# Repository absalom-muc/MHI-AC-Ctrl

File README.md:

# MHI-AC-Ctrl
Reads and writes data (e.g. power, mode, fan status etc.) from/to a Mitsubishi Heavy Industries (MHI) air conditioner (AC) via SPI controlled by MQTT. The AC is the SPI master and the ESP8266 is the SPI slave.

# Attention:
:warning: You have to open the indoor unit to have access to the SPI. Opening of the indoor unit should be done by 
a qualified professional because faulty handling may cause leakage of water, electric shock or fire! :warning: 

# Prerequisites:
For use of the program you have to connect your ESP8266 (I use a LOLIN(WEMOS) D1 R2 & mini with 80 MHz) via a
cable connector to your air conditioner. This has to be a split device (separated indoor and outdoor unit).
I assume that all AC units of the type "SRK xx ZS-S" / "SRC xx ZS-S" are supported. I use the indoor unit SRK 35 ZS-S and the outdoor unit SRC 35 ZS-S. Users reported that additionally the following models are supported:

- [SRF xx ZJX-S1](https://github.com/absalom-muc/MHI-AC-Ctrl/issues/17#issue-632187165)
- [SRF xx ZMX-S](https://github.com/absalom-muc/MHI-AC-Ctrl/issues/17#issuecomment-704789297)
- [SRF xx ZMXA-S](https://github.com/absalom-muc/MHI-AC-Ctrl/pull/91)
- SRF xx ZF-W
- [SRF xx ZS-W](https://github.com/absalom-muc/MHI-AC-Ctrl/pull/216#issue-3234769567) works with frame size 20
- [SRK xx ZJ-S](https://github.com/absalom-muc/MHI-AC-Ctrl/issues/10)
- [SRK xx ZM-S](https://github.com/absalom-muc/MHI-AC-Ctrl/issues/9)
- [SRK xx ZJX-S](https://github.com/absalom-muc/MHI-AC-Ctrl/issues/17#issuecomment-646469621)
- [SRK xx ZJX-S1](https://github.com/absalom-muc/MHI-AC-Ctrl/issues/17#issuecomment-646968940)
- [SRK xx ZR-WF](https://github.com/absalom-muc/MHI-AC-Ctrl/issues/214)
- [SRK xx ZRA-W](https://github.com/absalom-muc/MHI-AC-Ctrl/issues/17#issuecomment-730628655) / DXK xx ZRA-W
- [SRK xx ZSA-W](https://github.com/absalom-muc/MHI-AC-Ctrl/issues/17#issuecomment-891649495) / DXK xx ZSA-W
- [SRK63ZSPR-S](https://github.com/absalom-muc/MHI-AC-Ctrl/issues/149)
- SRK xx ZSXA-W/A
- [SRK xx ZSX-S](https://github.com/absalom-muc/MHI-AC-Ctrl/issues/6#issuecomment-582242372)
- [SRK xx ZSX-W](https://github.com/absalom-muc/MHI-AC-Ctrl/issues/17#issuecomment-643748095)
- [SRK xx ZS-W](https://github.com/absalom-muc/MHI-AC-Ctrl/issues/121)
- [SRK xx ZS-WF](https://github.com/absalom-muc/MHI-AC-Ctrl/issues/121#issuecomment-1938350129)
- [SRC 35Z SA-W]
- [DXK xx ZMA-S](https://github.com/absalom-muc/MHI-AC-Ctrl/issues/201)
- [SRK 2824 T (Japanese domestic model)](https://github.com/absalom-muc/MHI-AC-Ctrl/issues/211)

Unsupported models:
- [SRK71ZEA-S1](https://github.com/absalom-muc/MHI-AC-Ctrl/issues/143)
- [SRK35ZC-S](https://github.com/absalom-muc/MHI-AC-Ctrl/issues/154)
- [SRK xx ZSPR-S](https://github.com/absalom-muc/MHI-AC-Ctrl/issues/200) (except SRK63ZSPR-S)

If you find out that also other models are supported that are not listed here, please give feedback so that I can expand the list. In general, please recheck if your AC has a CNS connector before you spend time and money to build the hardware.

# Installing:

## Hardware:
The ESP8266 is powered from the AC via DC-DC (12V -> 5V) converter. 
The ESP8266 SPI signals SCL (SPI clock), MOSI (Master Out Slave In) and MISO (Master In Slave Out) are connected via a voltage level shifter 5V <-> 3.3V with the AC. Direct connection of the signals without a level shifter could damage your ESP8266!
More details are described in [Hardware.md](Hardware.md).

## Software:
The program uses the following libraries:
 - MQTT client library [PubSubClient3](https://github.com/hmueller01/pubsubclient3)
   - :warning: Don't use PubSubClient v2.8.0, it is broken due to issue [#747](https://github.com/knolleary/pubsubclient/issues/747) :warning:
 - [ArduinoOTA](https://github.com/esp8266/Arduino/tree/master/libraries/ArduinoOTA) (might be removed in future)
 
and optionally you need for the use of an external temperature sensor DS18x20 the libraries
 - [OneWire](https://www.pjrc.com/teensy/td_libs_OneWire.html)
 - [DallasTemperature](https://github.com/milesburton/Arduino-Temperature-Control-Library)

Please check the GitHub pages to see how to install them (usually via tools -> libraries).

Create a sub-directory "MHI-AC-Ctrl" and copy the files from the latest [release](https://github.com/absalom-muc/MHI-AC-Ctrl/releases) src directory in your MHI-AC-Ctrl sub-directory. You could also use the recently updated version in the [src folder](src) but with the risk that it is more unstable. The stability of the program is better when you compile it for a CPU frequency of 160MHz.
The configuration options are described in [SW-Configuration.md](SW-Configuration.md).

In a previous version (see [here](https://github.com/absalom-muc/MHI-AC-SPY)) I used the Hardware-SPI of the ESP8266. But since the SPI documentation of ESP8266 is poor, I decided to switch to a Software based SPI.
This Software based SPI is reliable and the performance of the ESP8266 is sufficient for this use case.
In case of problems please check the [Troubleshooting guide](Troubleshooting.md).

# Enhancement
If you are interested to have a deeper look on the SPI protocol or want to trace the SPI signals, please check [MHI-AC-Trace](https://github.com/absalom-muc/MHI-AC-Trace). But this is not needed for the standard user of MHI-AC-Ctrl.

# License
This project is licensed under the MIT License - see the LICENSE.md file for details

# Acknowledgments
The coding of the [SPI protocol](https://github.com/absalom-muc/MHI-AC-Trace/blob/main/SPI.md) of the AC is a nightmare. Without [rjdekker's MHI2MQTT](https://github.com/rjdekker/MHI2MQTT) I had no chance to understand the protocol! Unfortunately rjdekker is no longer active on GitHub. He used an Arduino plus an ESP8266 for his project.
Also thank you very much on the authors and contributors of [MQTT client](https://github.com/knolleary/pubsubclient), [ArduinoOTA](https://github.com/esp8266/Arduino/tree/master/libraries/ArduinoOTA), [OneWire](https://www.pjrc.com/teensy/td_libs_OneWire.html) and [DallasTemperature](https://github.com/milesburton/Arduino-Temperature-Control-Library) libraries.

Last but not least thank you for the implementation of MHI-AC-Ctrl in [different environments](https://github.com/absalom-muc/MHI-AC-Ctrl/blob/master/SW-Configuration.md#integration-examples) (FHEM, Tasmota, Home Assistant etc.)

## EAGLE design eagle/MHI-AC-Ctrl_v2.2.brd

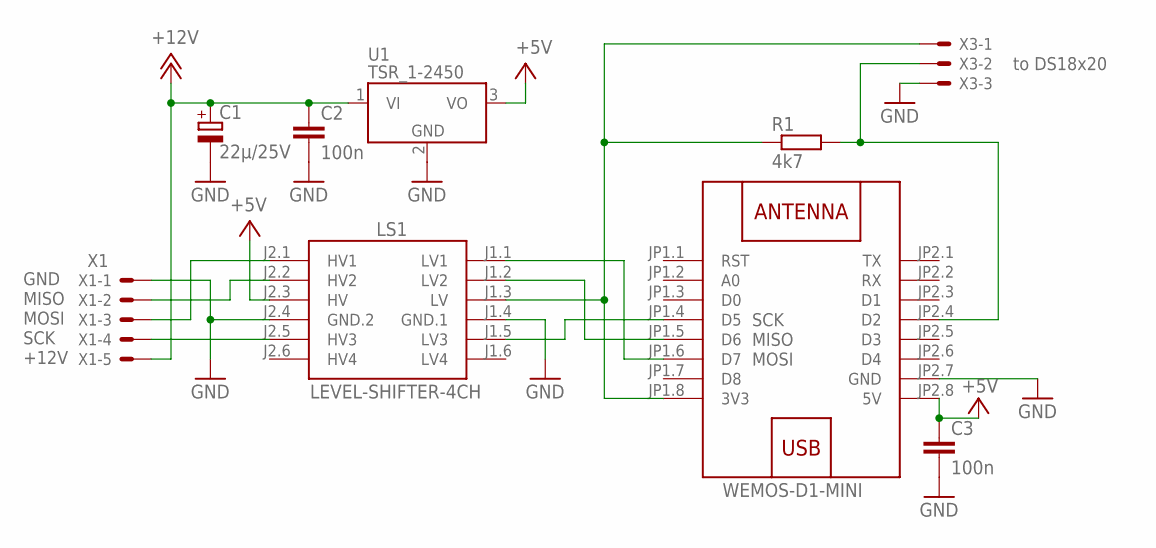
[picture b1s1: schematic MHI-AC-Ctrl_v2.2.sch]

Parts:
C1: 22µ/25V; E15-5
C2, C3: 100n; C025-024X044
LS1: LEVEL-SHIFTER-4CH
R1: 4k7; 0207/10
U1: TSR_1-2450; TSR-1
U$1: WEMOS-D1-MINI
X1: JST 03JQ-BT; JST-XH-05-PACKAGE-LONG-PAD
X3: JST-XH-03-PIN; JST-XH-03-ST90-PACKAGE-LONG-PAD

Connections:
+3V3: LS1.J1.3 (LV), R1.1, U$1.JP1.8 (3V3), X3.1
+5V: C3.1, LS1.J2.3 (HV), U1.3 (VO), U$1.JP2.8 (5V)
+12V: C1.+, C2.1, U1.1 (VI), X1.5
D2: R1.2, U$1.JP2.4 (D2), X3.2
GND: C1.-, C2.2, C3.2, LS1.J1.4 (GND.1), LS1.J2.4 (GND.2), U1.2 (GND), U$1.JP2.7 (GND), X1.1, X3.3
MISO: LS1.J2.2 (HV2), X1.2
MISO_LV: LS1.J1.2 (LV2), U$1.JP1.5 (D6)
MOSI: LS1.J2.1 (HV1), X1.3
MOSI_LV: LS1.J1.1 (LV1), U$1.JP1.6 (D7)
SCK: LS1.J2.5 (HV3), X1.4
SCK_LV: LS1.J1.5 (LV3), U$1.JP1.4 (D5)

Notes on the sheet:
MOSI
MISO
SCK
to DS18x20

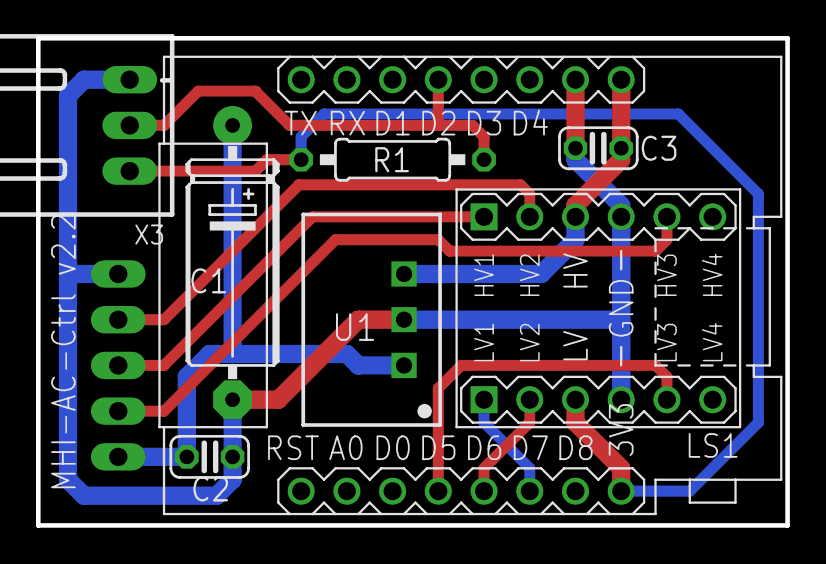
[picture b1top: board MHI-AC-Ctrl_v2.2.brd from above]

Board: 2 copper layers, 41.6 x 27.1 mm, 9 parts (1 on the bottom side), 11 nets.

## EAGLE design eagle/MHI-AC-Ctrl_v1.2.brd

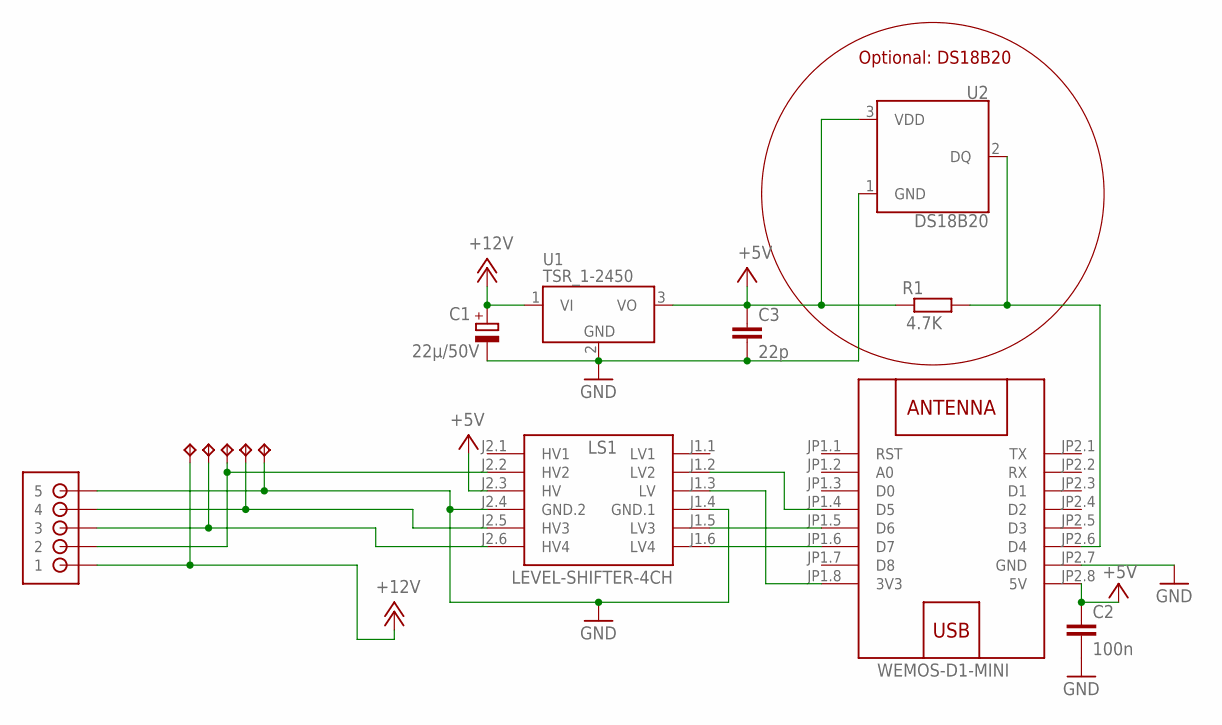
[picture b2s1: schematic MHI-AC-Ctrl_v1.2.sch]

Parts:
C1: 22µ/50V; E5-10,5
C2: 100n; C025-024X044
C3: 22p; C025-024X044
LS1: LEVEL-SHIFTER-4CH
R1: 4.7K; 0204/7
TP9, TP10, TP11, TP12, TP13: TPPAD1-13; P1-13
U1: TSR_1-2450; TSR-1
U2: DS18B20; TO-92-TO92127P495H2044-3
U$1: WEMOS-D1-MINI
U$4: JST-PH_5-PIN_HEADER; JST_B5B-PH_HEADER

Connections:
+3V3: LS1.J1.3 (LV), U$1.JP1.8 (3V3)
+5V: C2.1, C3.1, LS1.J2.3 (HV), R1.2, U1.3 (VO), U2.3 (VDD), U$1.JP2.8 (5V)
+12V: C1.+, TP13.TP, U1.1 (VI), U$4.P1 (1)
GND: C1.-, C2.2, C3.2, LS1.J1.4 (GND.1), LS1.J2.4 (GND.2), TP9.TP, U1.2 (GND), U2.1 (GND), U$1.JP2.7 (GND), U$4.P5 (5)
MISO: LS1.J2.5 (HV3), TP10.TP, U$4.P4 (4)
unnamed: LS1.J1.5 (LV3), U$1.JP1.5 (D6)
unnamed: LS1.J1.6 (LV4), U$1.JP1.6 (D7)
unnamed: LS1.J2.2 (HV2), TP11.TP, U$4.P2 (2)
unnamed: LS1.J2.6 (HV4), TP12.TP, U$4.P3 (3)
unnamed: R1.1, U2.2 (DQ), U$1.JP2.6 (D4)
SCL_LV: LS1.J1.2 (LV2), U$1.JP1.4 (D5)

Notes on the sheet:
Optional: DS18B20

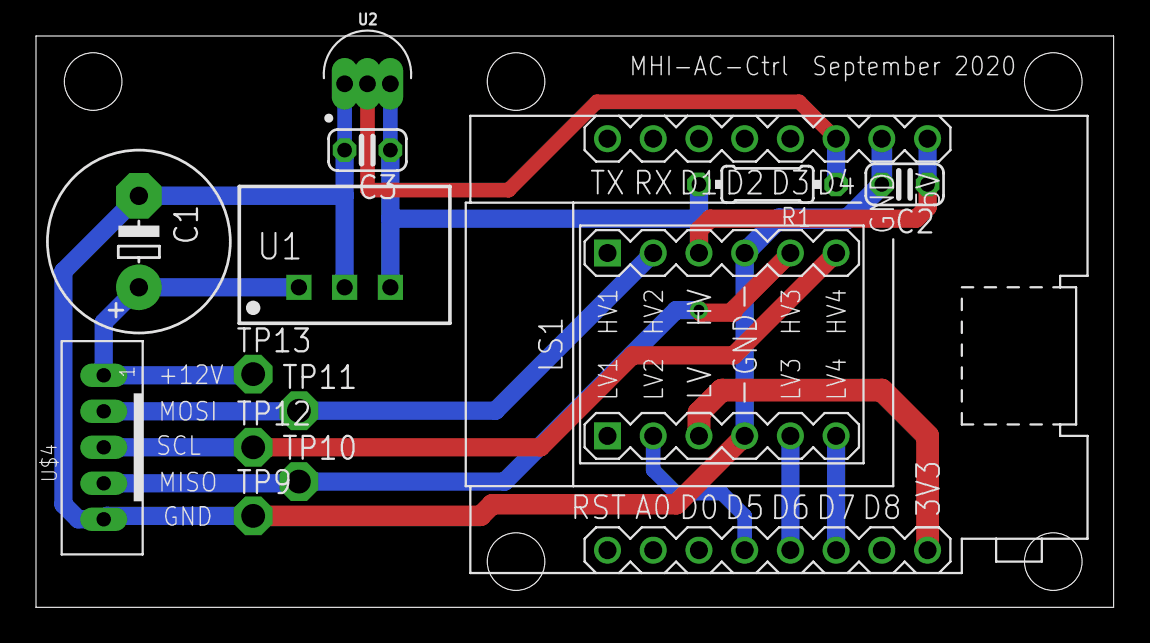
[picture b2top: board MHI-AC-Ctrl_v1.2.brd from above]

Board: 2 copper layers, 59.9 x 31.7 mm, 14 parts (0 on the bottom side), 11 nets.

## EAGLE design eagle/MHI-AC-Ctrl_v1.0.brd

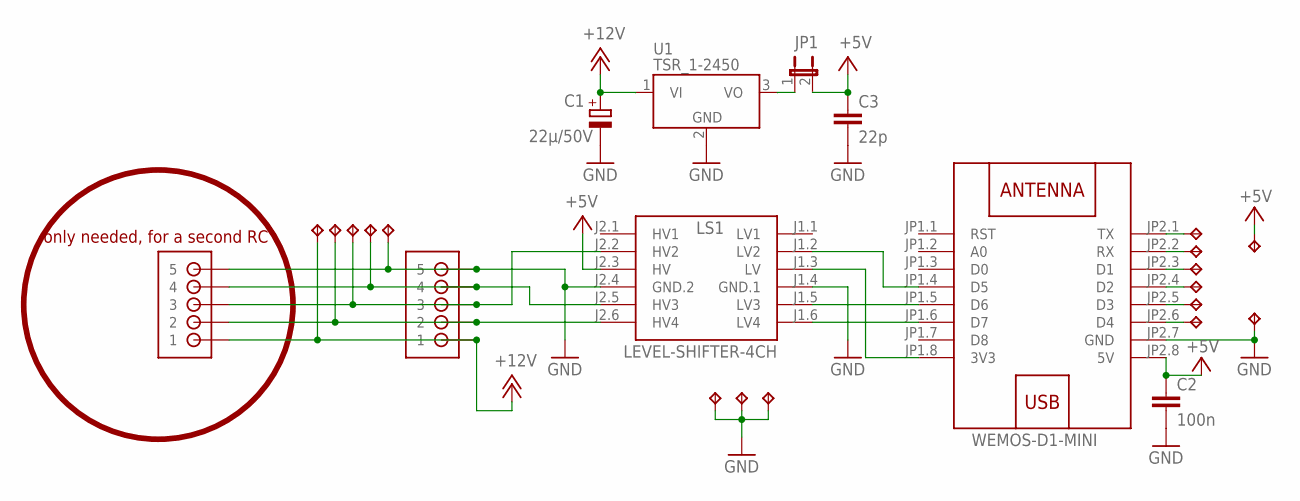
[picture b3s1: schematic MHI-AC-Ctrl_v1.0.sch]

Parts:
C1: 22µ/50V; E5-10,5
C2: 100n; C025-024X044
C3: 22p; C025-024X044
JP1: JP1E; JP1
LS1: LEVEL-SHIFTER-4CH
TP1, TP2, TP3, TP4, TP5, TP6, TP7, TP8, TP9, TP10, TP11, TP12, TP13, TP14, TP15, TP16: TPPAD1-13; P1-13
U1: TSR_1-2450; TSR-1
U$1: WEMOS-D1-MINI
U$4, U$5: JST-PH_5-PIN_HEADER; JST_B5B-PH_HEADER

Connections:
+3V3: LS1.J1.3 (LV), U$1.JP1.8 (3V3)
+5V: C2.1, C3.1, JP1.2, LS1.J2.3 (HV), TP8.TP, U$1.JP2.8 (5V)
+12V: C1.+, TP13.TP, U1.1 (VI), U$4.P1 (1), U$5.P1 (1)
GND: C1.-, C2.2, C3.2, LS1.J1.4 (GND.1), LS1.J2.4 (GND.2), TP7.TP, TP9.TP, TP14.TP, TP15.TP, TP16.TP, U1.2 (GND), U$1.JP2.7 (GND), U$4.P5 (5), U$5.P5 (5)
MISO: LS1.J2.5 (HV3), TP10.TP, U$4.P4 (4), U$5.P4 (4)
MISO_LV: LS1.J1.5 (LV3), U$1.JP1.5 (D6)
MOSI: LS1.J2.6 (HV4), TP12.TP, U$4.P2 (2), U$5.P2 (2)
MOSI_LV: LS1.J1.6 (LV4), U$1.JP1.6 (D7)
unnamed: TP1.TP, U$1.JP2.1 (TX)
unnamed: TP2.TP, U$1.JP2.2 (RX)
unnamed: TP3.TP, U$1.JP2.3 (D1)
unnamed: TP4.TP, U$1.JP2.4 (D2)
unnamed: TP5.TP, U$1.JP2.5 (D3)
unnamed: TP6.TP, U$1.JP2.6 (D4)
unnamed: JP1.1, U1.3 (VO)
SCL: LS1.J2.2 (HV2), TP11.TP, U$4.P3 (3), U$5.P3 (3)
SCL_LV: LS1.J1.2 (LV2), U$1.JP1.4 (D5)

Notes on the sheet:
only needed, for a second RC

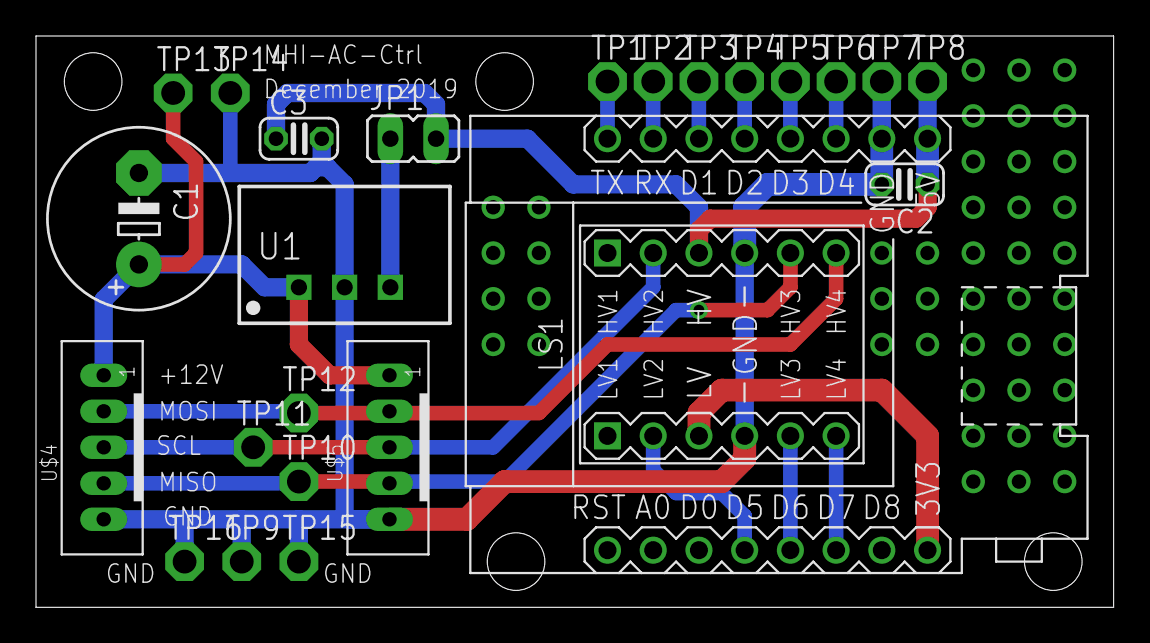
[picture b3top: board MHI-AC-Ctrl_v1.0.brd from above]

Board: 2 copper layers, 59.9 x 31.7 mm, 25 parts (0 on the bottom side), 17 nets.

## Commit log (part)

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2019-12-07 Create tmp
2019-12-15 update for v1.1
    Error code (DB4) added
    OTA is now also working when waiting for a MQTT connection
2019-12-17 Vanes information enhanced
    Due to update from niclet in the thread https://github.com/rjdekker/MHI2MQTT/issues/8#issuecomment-557870093
2019-12-21 some minor corrections
    clarification related to vanes
2019-12-21 configuration images added
2019-12-21 Showing different configurations
2019-12-21 not needed here
2019-12-21 Assembled PCB figure added
2020-01-18 update v1.2
    see Version.md
2020-01-20 Figures labeled
2020-01-20 Connection between AC and remote control clarified
2020-01-27 Fix logic error on MQTT connection failure backoff
2020-03-01 typos for v1.3 corrected
2020-03-01 link for src directory added
2020-03-01 typos corrected
2020-03-01 link to SPI.md added
2020-03-06 Clarification for Vanes status
2020-04-26 Timing diagram frame & byte
2020-04-26 timing diagram and timing values added
2020-04-26 cable connection diagram added
2020-05-14 Added changeable defs for Power and Mode states
2020-05-14 Operation date mode edits
2020-05-14 Updated MQTT readme with overrides
2020-05-14 Added OTA_NAME. Added MQTT_PREFIX example
2020-05-14 Corrected power and mode syntax
2020-06-05 update to v2.0
    see Version.md
2020-06-05 format issue resolved
2020-06-06 bug in row 192 fixed (wrong interrupt handler was selected)
    and some minor code rebuild
2020-06-07 unused variables removed
2020-06-07 write to AC simplified
2020-06-07 comment added
2020-06-12 added supported AC models
2020-06-14 1.Fix the pins are not match definition 2.Support for ESP-01
2020-06-14 Fix power on randomly
2020-06-15 Remove support for ESP-01
2020-06-15 Revert because it's still broken
2020-06-15 fix of issue #18 (AC Power off randomly)
    fix of issue #18 https://github.com/absalom-muc/MHI-AC-Ctrl/issues/18#issuecomment-643739863. The illegal (dummy) value 0xff from opdata was used for MISO_DB6. This led to the shutdown of the air con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
2020-06-15 List of supported AC models enhanced, SW installation description adapted
2020-06-18 link to error code document updated
2020-06-20 supported models added
2020-06-21 Create frequency_measurement.ino
    Used for measurement of the SCK period and byte/frame period
2020-06-24 SPI logger
    logs the timing of the SPI signal edges
2020-06-24 v2.01
    - No functional changes
    - Further reduction of memory usage
    - Compiler warnings removed
    - set-mechanism reworked
    - SCK by SCK_PIN replaced according to [pull request 19](https://github.com/absalom-muc/MHI-AC-Ctrl/pull/19)
    - Shift void MeasureFrequency() from support.cpp to MHI-AC-Ctrl-core.cpp
2020-06-24 v2.01
2020-06-28 update to v2.02
    Functionality for POWERON_WHEN_CHANGING_MODE enhanced, the according #define shifted to support.h
2020-06-28 typo in HOSTNAME corrected
2020-07-01 Made warning clearer not to use PubSubClient v2.8.0
2020-07-01 switched to vcd format
    use e.g. PulseView to see the waveform
2020-07-08 reference to Troubleshooting.md added
2020-07-09 updates for 2.03
    - Functionality for POWERON_WHEN_CHANGING_MODE improved in MHI-AC-Ctrl.ino
    - WiFi mode restricted to STA (no more AP) in support.cpp
2020-07-09 info for fan auto added
2020-07-09 update to v2.1
    generation of vcd improved
2020-07-27 Another supported model
    Hi absalom, thank you very much for this project.
    I successfully installed your adapter yesterday.
    My MHI model is: **SRK 35 ZS-W**
2020-07-27 Fixing link to SERVICE SUPPORT HANDBOOK
2020-07-27 Another supported model (#35)
    Hi absalom, thank you very much for this project.
    I successfully installed your adapter yesterday.
    My MHI model is: **SRK 35 ZS-W**
2020-07-29 link related to the meaning of the operating data updated based on pull request #36
    see pull request https://github.com/absalom-muc/MHI-AC-Ctrl/pull/36
2020-07-29 important warning related to the 2-pin connector added
2020-08-09 external temperature sensor disabled per default
    according to issue 32 in https://github.com/absalom-muc/MHI-AC-Ctrl/issues/32
2020-08-28 link to Gerber files added
2020-09-07 - refactored board
2020-09-10 - updatet HW infos
2020-09-11 - add openhab documentation example
2020-09-11 - link to SW-Configuration.md
2020-09-11 invert pin 2 and 3, remove AIRWIRE from DS18x20
2020-10-07 MHI AC model added
2020-11-20 SRK xx ZRA-W added
2021-01-18 Update hrponline hint document link
    Fixed broken link
2021-01-18 Update hrponline hint document link (#52)
    Fixed broken link
2021-02-06 PCB layout update
2021-02-06 comment related to draft SW status removed
2021-04-01 link to swapped pins on PCB removed
    No longer needed due to new PCB layout
2021-04-27 Added unsupported model
    SRKxxZSPR-S doesn’t have the required connector
2021-04-28 Added unsupported model (#57)
    SRKxxZSPR-S doesn’t have the required connector
2021-05-15 added some integration examples
2021-08-30 Made WiFi SSID, hostname and MQTT server dynamic
2021-09-10 Update SW-Configuration.md
    Added integration example for ESPHome and "WiFi SSID, hostname and MQTT server dynamic"
2021-09-10 Added reference to different implementations
2021-09-28 v2.3, see Version.md
2021-11-13 update 2.5R1
    see Version.md
2021-12-17 v2.5R21
    - calculation of RETURN-AIR in MHI-AC-Ctrl.ino corrected
    - Removed the option #define ROOM_TEMP_IU for adaption by the user in support.h. Now it is generated automatically when ROOM_TEMP_DS18X20 and ROOM_TEMP_MQTT are not defined
    - Reworked WiFi network re-scan function
2021-12-18 link to MHI-AC-Trace added
    SPI.md removed here and shifted to MHI-AC-Trace repository
2022-04-14 added voltage measurement for SCK/MOSI
2022-05-24 Update README.md
    Add to supported models list
2022-05-24 Update README.md (#91)
    Add to supported models list
2022-05-29 Update issue templates
2022-06-04 Update README.md
    added SRF xx ZS-W
2022-06-07 Resolution for Tsetpoint added
2022-06-09 update to v2.5R3
    see Version.md for details
2022-06-16 reference added to discussion if the level shifter can be omitted
2022-08-28 update 2.6R2
    mainly Fan with "Auto" implemented
2022-10-25 kicad: Redo v2.2 in KiCad
    As KiCad has become quite popular (and eagle less so) offer the same
    design in KiCad going forward.
2022-10-31 kicad: Redo v2.2 in KiCad (#106)
    As KiCad has become quite popular (and eagle less so) offer the same
    design in KiCad going forward.
2022-10-31 KiCad PCB added
2022-11-03 Enhanced explanation for ROOM_TEMP_MQTT_TIMEOUT
2022-11-05 note for the KiCad PCB added
2022-11-09 kicad: Move connector to the bottom of the PCB
    This changes the appearance of the connector only! The pin-out remains
    identical, the gerbers, identical. Only the location of the connector
    moved, which causes the silkscreen to change and the 3D render.
2022-11-13 Added details of the error codes and description how to add log files
2022-12-18 Added description of ENHANCED_RESOLUTION
2022-12-20 Removed Troom_offset topic
2022-12-21 update to v2.6R3
    Added switch for Troom filtering
2022-12-21 update v2.6R4
    Added Enhance resolution of Tsetpoint
2022-12-21 Added hint that 160MHz CPU frequency should be used for compile
2022-12-22 changed TEMP_MEASURE_PERIOD to default value 0
2022-12-22 update to v2.6R5 (added ROOM_TEMP_DS18X20_OFFSET)
2022-12-23 Fixed section 'Enhance resolution of Tsetpoint'
2023-01-28 Update for 2.6 release
    see Version.md
2023-01-29 Fix for fan not showing 4 and Auto after powerdown AC
2023-02-11 Added version.md and support.h
2023-02-11 Fix for fan not showing 4 and Auto after powerdown AC (#132)
    * Fix for fan not showing 4 and Auto after powerdown AC
    * Added version.md and support.h
2023-03-04 Added Energy used in kWH
2023-03-05 Added Energy used in kWH (#135)
2023-03-05 version fixed
2023-03-26 Change MISO sending and avoid jitter
    - fix some compiler warnings by [glsf91](https://github.com/glsf91)
    - change sending MISO with faster refresh of data every 20s by [glsf91](https://github.com/glsf91)
    - avoid jitter with internal temperature sensor, now updating atmost every 5s by [glsf91](https://github.com/glsf91)
    - fix print wifi encryption type by [glsf91](https://github.com/glsf91)
    - skip not usable values for DB18B20 by [glsf91](https://github.com/glsf91)
2023-07-19 Try to get rid of room temperatures of 48,25 °C
    In my Home assistant environment, I got some random spikes of 48,25 °C, which were disturbing the charts.
2023-07-19 Accidentally removed the opening curly bracket
2023-08-05 reworked list of supported models
    added a link to each supported model to make it more comphrehensible
2023-08-28 KiCad: Fix J1 connector
    This fixes the J1 connector footprint and 3D model by using
    easyeda2kicad [0] to pull the data from LCSC!
    Closes #111
    [0]: https://github.com/uPesy/easyeda2kicad.py
2023-08-28 KiCad: Fix J1 connector (#155)
    This fixes the J1 connector footprint and 3D model by using
    easyeda2kicad [0] to pull the data from LCSC!
    Closes #111
    [0]: https://github.com/uPesy/easyeda2kicad.py
2023-09-28 Added 3D auto and vanes L/R
    Added 3D auto and vanes L/R. You have to enable this.
2023-10-02 Some cosmetic issues
2023-10-02 Resolved cosmetic issue
2023-10-23 Add SRC35ZSA-W to supported model list
    I've built and installed several of these units from the Gerber files on
    the website via JLC-PCB and have full functionality with this model.
2023-10-26 Update SW-Configuration.md
    Added description Errorcode topic
2023-10-26 Fix link
2023-11-27 Added HA in SW-Configuration.md
2023-11-28 Correct J1 connector pinout
    Fixes #167
    Regenerated PDF and gerber/drill
2024-01-08 Correct J1 connector pinout (#168)
    Fixes #167
    Regenerated PDF and gerber/drill
2024-01-12 Update SW-Configuration.md
    Added Display AC controller to integration list
2024-01-15 Update SW-Configuration.md. Replaced MQTT Errorcode topic
    Changed MQTT Errorcode topic to MQTT operating data PROTECTION-NO topic because of wrong description.
2024-02-07 git: Enable LFS for PDF files
    No need to track datasheets.
2024-02-08 remove: Drop generateable files
    Delete generatable files, as we should just generate them from a pipeline.
    In addition, the pdf makes it impossible to enable git lfs for binary files.
2024-02-12 Add info on compatibility with SRK xx ZS-WF models.
2024-02-12 Added SRK xx ZS-WF to supported models
2024-04-13 Added SRK 25 ZSPR-S to unsupported list
2024-05-31 Add alternate supported model numbers in README
    SRK and DXK are the same in the ZRA-W/ZSA-W series.
2024-06-15 Added link to esp32 variant in Hardware.md
2024-08-28 Fork off hardware to seperate repo
    It is increasingly becoming more difficult to keep track of hardware and
    software changes. E.g. git-tags refer to software, but the hardware also
    has versions.
    To reduce the scope of this repository, and make things cleaner
    repository wise, lets split off these two repositories into software and
    hardware.
2024-08-30 Update Hardware.md Kicad
2024-11-06 changed SRK63ZSPR-S supported and SRK xx ZSPR-S unsupported
2024-11-14 Added DXKxxZMA-S as supported
2025-03-06 Fix emoji warning
2025-03-26 Add note about loss of timer functionality in troubleshooting
2025-03-26 Rephrase note about loss of timer functionality
2025-06-16 docs: move from unmaintained knolleary/pubsubclient to hmueller01/pubsubclient3
2025-07-03 AddedMHI SRKxxZR-WF
2025-07-16 Add support for SRF xx ZS-W series to the readme
2025-11-19 Update README.md
    path to pull request added
2025-11-19 Add validated support for SRF xx ZS-W series to the readme (#216)
    * Add support for SRF xx ZS-W series to the readme
    * Update README.md
    path to pull request added
    ---------
2025-11-19 docs: move from unmaintained knolleary/pubsubclient to hmueller01/pubsubclient3 (#212)

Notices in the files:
parts and their libraries:
diy-modules: Released under the Creative Commons Attribution 4.0 International License: http://creativecommons.org/licenses/by/4.0
